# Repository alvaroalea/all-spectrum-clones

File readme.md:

# Esquema electrico en Kicad de Clones de Sinclair ZX Spectrum

La idea es que a base de borrar trozos de circuito que no interese, generemos nuestro propio clon
personalizado con las siguientes opciones:
 
* ULA - Elegir entre ALTERA o XILING
* MEMORIA RAM- 48 o 128K de RAM
* MEMORIA ROM- 16K o 64K ROM, opciones de ROM mayores con seleccion por dip-switches
* SONIDO - PSG (AY-3-8912 o YM2114), MONO O ABC, OPCION puertos SERIE, AUX
* CINTA - conectores 48K o +3, circuiteria tipo Arlequin o tipo Humble
* VIDEO - RGB o Composite, circuiteria tipo Arlequin
* JOYSTICK - SJS o ATARI, normas SINCLAIR o KEMPSTON
* TECLADO - integrado de 40 Teclas, por transistores (arlequin) o diodos
* TECLADO - conexion facil para teclas externas, DEL, BREAK, CURSORES, BLOQ SHIFT, EXTRA, GRAF
* DISCO - Conexion para interfaz multisistema de wilco (compatible +3), interfaz +D o Interfaz +3
* ALMACENAMIENTO - Interfaz IDE de 8bits, Cartucho IF2, dandanator integrado o con cartuchos VC2.0 

## Futuro:
* DISCO - beta 128, ZXMMC, DIVIDE
* MEMORIA - Usar los 256K tipo ruso
* VIDEO - conector euroconector
* ULA - por chips del arlequin
* IMPRESORA - amstrad / kempston
* RATON - kempston db9, kempston ps2

## Ejemplos:

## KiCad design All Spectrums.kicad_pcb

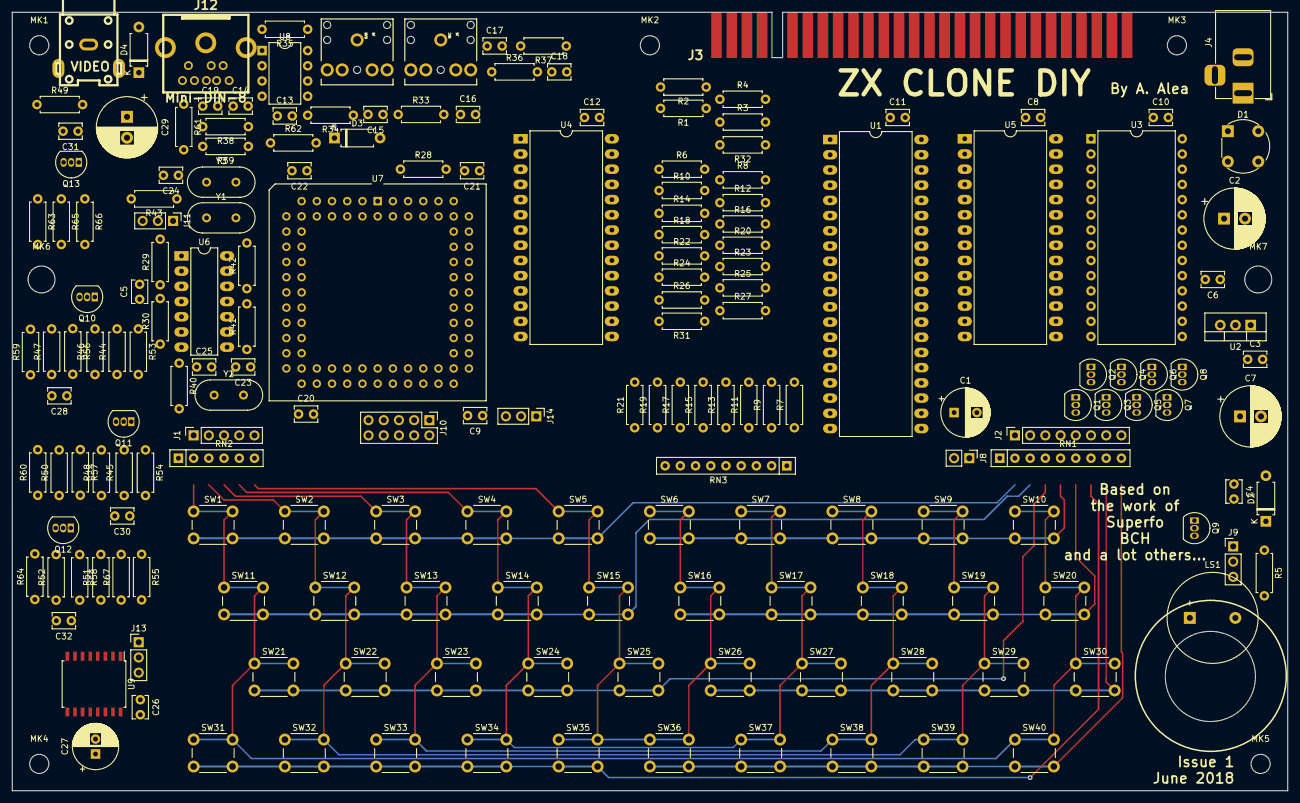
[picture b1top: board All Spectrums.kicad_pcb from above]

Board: 2 copper layers, 213.0 x 130.0 mm, 193 parts (0 on the bottom side), 148 nets.

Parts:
C1: CP; CP_Radial_D8.0mm_P3.80mm
C2: 680u; CP_Radial_D10.0mm_P3.50mm
C3, C4, C5, C6, C8, C9, C10, C11, C12, C13, C15, C17, C19, C20, C21, C22, C23, C25, C26, C28, C30, C31, C32: 100n; C_Disc_D3.8mm_W2.6mm_P2.50mm
C7, C29: 220u; CP_Radial_D10.0mm_P3.50mm
C14, C16: 1n; C_Disc_D3.8mm_W2.6mm_P2.50mm
C18: 3.3n; C_Disc_D3.8mm_W2.6mm_P2.50mm
C24: 10p; C_Disc_D3.8mm_W2.6mm_P2.50mm
C27: 10u; CP_Radial_D7.5mm_P2.50mm
D1: D_Bridge_+-AA; Diode_Bridge_Round_D8.9mm
D2: 1N4148; D_A-405_P7.62mm_Horizontal
D3: 1N4047a; D_A-405_P7.62mm_Horizontal
D4: 1N4742a; D_A-405_P7.62mm_Horizontal
J1: Conn_01x05; PinSocket_1x05_P2.54mm_Vertical
J2: Conn_01x08; PinSocket_1x08_P2.54mm_Vertical
J3: ZX_Spectrum_Connector_plus3_SORTED; ZX_EDGE
J4: Jack-DC; BarrelJack_Horizontal
J5: EAR; AUDIO-JACK
J6: MIC; AUDIO-JACK
J7: VIDEO; rca_yellow
J8: RESET; PinHeader_1x02_P2.54mm_Vertical
J9, J11, J13, J14: Conn_01x03; PinHeader_1x03_P2.54mm_Vertical
J10: JTAG; PinHeader_2x05_P2.54mm_Vertical
J12: Mini-DIN-8; minidin-8
LS1: Speaker; Buzzer_15x7.5RM7.6
MK1, MK2, MK3, MK4, MK5: MountingHole_3.2mm_M3
MK6, MK7: MountingHole_4.5mm
Q1, Q2, Q3, Q4, Q5, Q6, Q7, Q8: BC557; TO-92_Inline
Q9, Q10, Q11, Q12, Q13: BC548; TO-92_Inline
R1, R2, R3, R4, R34, R63: 10K; R_Axial_DIN0207_L6.3mm_D2.5mm_P7.62mm_Horizontal
R5: 22K; R_Axial_DIN0207_L6.3mm_D2.5mm_P7.62mm_Horizontal
R6, R7, R8, R9, R10, R11, R12, R13, R14, R15, R16, R17, R18, R19, R20, R21, R22, R23, R24, R25, R26, R27, R28, R29, R30, R31, R32, R35, R40, R41, R42: 470; R_Axial_DIN0207_L6.3mm_D2.5mm_P7.62mm_Horizontal
R33, R37, R39: 12K; R_Axial_DIN0207_L6.3mm_D2.5mm_P7.62mm_Horizontal
R36: 33K; R_Axial_DIN0207_L6.3mm_D2.5mm_P7.62mm_Horizontal
R38: 100K; R_Axial_DIN0207_L6.3mm_D2.5mm_P7.62mm_Horizontal
R43: 4M7; R_Axial_DIN0207_L6.3mm_D2.5mm_P7.62mm_Horizontal
R44, R45: 18K; R_Axial_DIN0207_L6.3mm_D2.5mm_P7.62mm_Horizontal
R46, R48, R51: 3K9; R_Axial_DIN0207_L6.3mm_D2.5mm_P7.62mm_Horizontal
R47, R50, R52, R59, R60, R64: 68; R_Axial_DIN0207_L6.3mm_D2.5mm_P7.62mm_Horizontal
R49, R56, R57, R58, R67: 75; R_Axial_DIN0207_L6.3mm_D2.5mm_P7.62mm_Horizontal
R53, R54, R55: 2K2; R_Axial_DIN0207_L6.3mm_D2.5mm_P7.62mm_Horizontal
R61, R65, R66: 270; R_Axial_DIN0207_L6.3mm_D2.5mm_P7.62mm_Horizontal
R62: 150; R_Axial_DIN0207_L6.3mm_D2.5mm_P7.62mm_Horizontal
RN1, RN3: R_Network08; R_Array_SIP9
RN2: R_Network05; R_Array_SIP6
SW1: KEY_1; SW_PUSH_6mm_H5mm
SW2: KEY_2; SW_PUSH_6mm_H5mm
SW3: KEY_3; SW_PUSH_6mm_H5mm
SW4: KEY_4; SW_PUSH_6mm_H5mm
SW5: KEY_5; SW_PUSH_6mm_H5mm
SW6: KEY_6; SW_PUSH_6mm_H5mm
SW7: KEY_7; SW_PUSH_6mm_H5mm
SW8: KEY_8; SW_PUSH_6mm_H5mm
SW9: KEY_9; SW_PUSH_6mm_H5mm
SW10: KEY_10; SW_PUSH_6mm_H5mm
SW11: KEY_Q; SW_PUSH_6mm_H5mm
SW12: KEY_W; SW_PUSH_6mm_H5mm
SW13: KEY_E; SW_PUSH_6mm_H5mm
SW14: KEY_R; SW_PUSH_6mm_H5mm
SW15: KEY_T; SW_PUSH_6mm_H5mm
SW16: KEY_Y; SW_PUSH_6mm_H5mm
SW17: KEY_U; SW_PUSH_6mm_H5mm
SW18: KEY_I; SW_PUSH_6mm_H5mm
SW19: KEY_O; SW_PUSH_6mm_H5mm
SW20: KEY_P; SW_PUSH_6mm_H5mm
SW21: KEY_A; SW_PUSH_6mm_H5mm
SW22: KEY_S; SW_PUSH_6mm_H5mm
SW23: KEY_D; SW_PUSH_6mm_H5mm
SW24: KEY_F; SW_PUSH_6mm_H5mm
SW25: KEY_G; SW_PUSH_6mm_H5mm
SW26: KEY_H; SW_PUSH_6mm_H5mm
SW27: KEY_J; SW_PUSH_6mm_H5mm
SW28: KEY_K; SW_PUSH_6mm_H5mm
SW29: KEY_L; SW_PUSH_6mm_H5mm
SW30: KEY_ENTER; SW_PUSH_6mm_H5mm
SW31: KEY_SHIFT; SW_PUSH_6mm_H5mm
SW32: KEY_Z; SW_PUSH_6mm_H5mm
SW33: KEY_X; SW_PUSH_6mm_H5mm
SW34: KEY_C; SW_PUSH_6mm_H5mm
SW35: KEY_V; SW_PUSH_6mm_H5mm
SW36: KEY_B; SW_PUSH_6mm_H5mm
SW37: KEY_N; SW_PUSH_6mm_H5mm
SW38: KEY_M; SW_PUSH_6mm_H5mm
SW39: KEY_SYMB; SW_PUSH_6mm_H5mm
SW40: KEY_SPACE; SW_PUSH_6mm_H5mm
U1: Z80CPU; DIP-40_W15.24mm_LongPads
U2: L7805; TO-220-3_Vertical
U3: 27128; DIP-28_W15.24mm
U4, U5: 62256; DIP-28_W15.24mm_LongPads
U6: 74HC04; DIP-14_W7.62mm_LongPads
U7: EPM7128S_LCC; PLCC-84_THT-Socket
U8: TL712; DIP-8_W7.62mm
U9: AD725; SOIC-16W_7.5x10.3mm_P1.27mm
Y1: 14.000Mhz; Crystal_HC18-U_Vertical
Y2: 3.58Mhz; Crystal_HC18-U_Vertical
Y3: 4.433Mhz; Crystal_HC18-U_Vertical

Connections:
+5V: C3.1, C7.1, C8.2, C9.2, C10.2, C11.2, C12.2, C13.1, C20.2, C21.2, C22.2, C25.2, C26.2, C27.1, D3.1, J3.A3, J10.4, J13.1, J14.1, Q9.1, Q10.1, Q11.1, Q12.1, Q13.1, R1.1, R2.1, R3.1, R4.1, R40.2, R61.2, RN1.1, RN2.1, RN3.1, U1.11, U2.3, U3.1, U3.27, U3.28, U4.28, U5.28, U6.14, U7.13, U7.26, U7.38, U7.53, U7.66, U7.78, U8.4, U8.8, U9.4, U9.5, U9.14, U9.15
+9V: C2.1, C6.1, D1.1, J3.A4, R62.2, U2.1
/ula/TCK: J10.1, U7.62
/ula/TDI: J10.9, U7.14
/ula/TDO: J10.3, U7.71
/ula/TMS: J10.5, U7.23
A0: J3.A9, R6.2, U1.30, U3.10, U5.10, U7.8
A1: J3.A10, R8.2, U1.31, U3.9, U5.9
A2: J3.A11, R10.2, U1.32, U3.8, U5.8
A3: J3.A12, R12.2, U1.33, U3.7, U5.7
A4: J3.A24, R14.2, U1.34, U3.6, U5.6
A5: J3.A23, R16.2, U1.35, U3.5, U5.5
A6: J3.A22, R18.2, U1.36, U3.4, U5.4
A7: J3.A21, R20.2, U1.37, U3.3, U5.3
A8: J3.B26, Q6.2, R22.2, U1.38, U3.25, U5.25
A9: J3.A27, Q3.2, R23.2, U1.39, U3.24, U5.24
A10: J3.B27, Q2.2, R24.2, U1.40, U3.21, U5.21
A11: J3.A28, Q1.2, R25.2, U1.1, U3.23, U5.23
A12: J3.A2, Q4.2, R26.2, U1.2, U3.2, U5.2
A13: J3.B2, Q5.2, R27.2, U1.3, U3.26, U5.26
A14: J3.A1, Q7.2, U1.4, U5.1, U7.49
A15: J3.B1, Q8.2, U1.5, U7.48
AUDIO_OUT: C19.2, J12.5
B: Q12.3, R52.2, R64.2
BUSACK: J3.A26, U1.23
BUSRQ: J3.A19, R4.2, U1.25
CLK: R1.2, U1.6, U7.45
CLK14: U6.6, U7.83
CLK_B: J3.A8, U7.46
D0: J3.B6, R7.1, RN3.2, U1.14, U3.11, U5.11
D1: J3.B7, R9.1, RN3.3, U1.15, U3.12, U5.12
D2: J3.B8, R11.1, RN3.4, U1.12, U3.13, U5.13
D3: J3.B11, R13.1, RN3.5, U1.8, U3.15, U5.15
D4: J3.B12, R15.1, RN3.6, U1.7, U3.16, U5.16
D5: J3.B10, R17.1, RN3.7, U1.9, U3.17, U5.17
D6: J3.B9, R19.1, RN3.8, U1.10, U3.18, U5.18
D7: J3.B3, R21.1, RN3.9, U1.13, U3.19, U5.19
EAR: C4.1, R38.1, U7.44, U8.6
G: Q11.3, R50.2, R60.2
GND: C1.2, C2.2, C3.2, C6.2, C7.2, C8.1, C9.1, C10.1, C11.1, C12.1, C13.2, C16.2, C18.2, C20.1, C21.1, C22.1, C24.1, C25.1, C26.1, C27.2, D1.2, D4.2, J3.A6, J3.A7, J3.A14, J7.2, J8.1, J9.3, J10.2, J10.10, J12.1, J13.3, J14.3, LS1.2, Q1.1, Q2.1, Q3.1, Q4.1, Q5.1, Q6.1, Q7.1, Q8.1, R34.2, R43.1, R53.1, R54.1, R55.1, R56.1, R57.1, R58.1, R66.1, U1.29, U2.2, U3.14, U4.1, U4.14, U5.14, U6.7, U7.3, U7.7, U7.19, U7.32, U7.42, U7.43, U7.47, U7.59, U7.72, U7.82, U8.5, U9.2, U9.12, U9.13, Y3.2
HALT: J3.B15, U1.18
INT: J3.B13, R31.1, U1.16
IORQ: J3.B17, R28.1, U1.20, U7.2, U7.77
IORQULA: J3.A13, R28.2, U7.84
KB0: J1.1, RN2.2, SW1.1, SW10.1, SW11.1, SW20.1, SW21.1, SW30.1, SW31.1, SW40.1, U7.70
KB1: J1.2, RN2.3, SW2.1, SW9.1, SW12.1, SW19.1, SW22.1, SW29.1, SW32.1, SW39.1, U7.74
KB2: J1.3, RN2.4, SW3.1, SW8.1, SW13.1, SW18.1, SW23.1, SW28.1, SW33.1, SW38.1, U7.73
KB3: J1.4, RN2.5, SW4.1, SW7.1, SW14.1, SW17.1, SW24.1, SW27.1, SW34.1, SW37.1, U7.75
KB4: J1.5, RN2.6, SW5.1, SW6.1, SW15.1, SW16.1, SW25.1, SW26.1, SW35.1, SW36.1, U7.76
M1: J3.B24, U1.27
MIC: R36.1, U7.40
MREQ: J3.B16, U1.19, U7.5
NMI: J3.B14, R2.2, U1.17
unnamed: C4.2, R5.1
unnamed: C5.1, R30.2, U6.3
unnamed: C5.2, R29.1, U6.2
unnamed: C14.1, U8.3
unnamed: C14.2, C15.2, R35.2, U8.2
unnamed: C15.1, D3.2, R33.1
unnamed: C16.1, R33.2, R34.1
unnamed: C17.2, C18.1, R36.2, R37.2
unnamed: C19.1, R38.2, R39.2
unnamed: C23.1, R42.2, U6.11
unnamed: C23.2, R41.1, U6.8
unnamed: C24.2, J11.3, R43.2, Y3.1
unnamed: C28.1, U9.6
unnamed: C28.2, R47.1, R56.2
unnamed: C29.1, C31.1, U9.10
unnamed: C29.2, C31.2, R49.1
unnamed: C30.1, U9.7
unnamed: C30.2, R50.1, R57.2
unnamed: C32.1, U9.8
unnamed: C32.2, R52.1, R58.2
unnamed: D1.3, J4.1
unnamed: D1.4, J4.2
unnamed: D2.1, Q9.2, R5.2
unnamed: D4.1, J12.2, R62.1
unnamed: J7.1, R49.2
unnamed: J9.1, Q9.3
unnamed: J9.2, LS1.1
unnamed: J11.1, R40.1, U6.12
unnamed: J12.3, R61.1
unnamed: J12.4, R60.1
unnamed: J12.6, R59.1
unnamed: J12.7, R64.1
unnamed: J12.8, R65.1
unnamed: Q10.2, R44.1, R46.1, R53.2
unnamed: Q11.2, R45.1, R48.1, R54.2
unnamed: Q12.2, R51.1, R55.2, R67.1
unnamed: Q13.2, R63.1, U9.16
unnamed: Q13.3, R65.2, R66.2
unnamed: R29.2, U6.1, Y1.1
unnamed: R30.1, U6.4, U6.5, Y1.2
unnamed: R31.2, U7.80
unnamed: R32.2, U7.79
unnamed: R35.1, U8.7
unnamed: R41.2, U6.9, Y2.1
unnamed: R42.1, U6.10, U6.13, Y2.2
P-N_CLK: J11.2, U9.3
P-N_ULA: J14.2, U7.58
P-N_VCHIP: J13.2, U9.1
R: Q10.3, R47.2, R59.2
RAM_CS: U5.20, U7.81
RD: J3.B18, U1.21, U3.22, U5.22, U7.4
RFSH: J3.B25, U1.28
ROM_CS: J3.A25, R32.1, U3.20
S0: J2.1, Q1.3, RN1.2, SW1.2, SW2.2, SW3.2, SW4.2, SW5.2
S1: J2.2, Q2.3, RN1.3, SW11.2, SW12.2, SW13.2, SW14.2, SW15.2
S2: J2.3, Q3.3, RN1.4, SW21.2, SW22.2, SW23.2, SW24.2, SW25.2
S3: J2.4, Q4.3, RN1.5, SW6.2, SW7.2, SW8.2, SW9.2, SW10.2
S4: J2.5, Q5.3, RN1.6, SW16.2, SW17.2, SW18.2, SW19.2, SW20.2
S5: J2.6, Q6.3, RN1.7, SW31.2, SW32.2, SW33.2, SW34.2, SW35.2
S6: J2.7, Q7.3, RN1.8, SW26.2, SW27.2, SW28.2, SW29.2, SW30.2
S7: J2.8, Q8.3, RN1.9, SW36.2, SW37.2, SW38.2, SW39.2, SW40.2
SPK: D2.2, R37.1, R39.1, U7.50
VA0: R6.1, U4.10, U7.21
VA1: R8.1, U4.9, U7.22
VA2: R10.1, U4.8, U7.24
VA3: R12.1, U4.7, U7.29
VA4: R14.1, U4.6, U7.31
VA5: R16.1, U4.5, U7.34
VA6: R18.1, U4.4, U7.33
VA7: R20.1, U4.3, U7.37
VA8: R22.1, U4.25, U7.36
VA9: R23.1, U4.24, U7.30
VA10: R24.1, U4.21, U7.25
VA11: R25.1, U4.23, U7.28
VA12: R26.1, U4.2, U7.41
VA13: R27.1, U4.26, U7.35
VD0: R7.2, U4.11, U7.16
VD1: R9.2, U4.12, U7.15
VD2: R11.2, U4.13, U7.10
VD3: R13.2, U4.15, U7.9
VD4: R15.2, U4.16, U7.11
VD5: R17.2, U4.17, U7.12
VD6: R19.2, U4.18, U7.17
VD7: R21.2, U4.19, U7.18
VRAM_CS: U4.20, U7.20
VRAM_RD: U4.22, U7.27
VRAM_WR: U4.27, U7.39
WAIT: J3.B21, R3.2, U1.24
WR: J3.B19, U1.22, U5.27, U7.6
blue: R51.2, U7.57
bright: R44.2, R45.2, R67.2, U7.51
green: R48.2, U7.54
red: R46.2, U7.55
sync: R63.2, U7.56
~RESET: C1.1, J3.A20, J8.2, U1.26, U7.1

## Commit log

2018-06-12 Inicial
2018-06-12 more pics
2018-06-18 add plus 3 disk interface
